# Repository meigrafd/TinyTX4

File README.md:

TinyTX4
=======

RFM12B based TinyTX Transmitter

Projekt Page: http://www.forum-raspberrypi.de/Thread-messen-steuern-regeln-batteriebetriebene-funk-sensoren

## Compiled Sketch size

#### with RFM12B lib:

Send_DHT22.ino --> 5.254 Bytes.  
Send_DHT22.ino & encrypt --> 6.896 Bytes.  
Send_DHT22_Watchdog.ino --> 5.512 Bytes.  
Send_DHT22_Watchdog.ino & encrypt --> 7.154 Bytes.  

Send_DS18B20.ino --> 7.342 Bytes.  
Send_DS18B20.ino & encrypt --> ... 768 bytes to big.  
Send_DS18B20_Watchdog.ino --> 7.590 Bytes.  
Send_DS18B20_Watchdog.ino & encrypt --> ... 1012 bytes to big.  

Send_ReedSwitch_Watchdog.ino --> 4.312 Bytes.  
Send_ReedSwitch_Watchdog.ino & encrypt --> 5.954 Bytes.  

#### with JeeLib:

Send_DHT22_Watchdog_JeeLib.ino --> 5.082 Bytes.  
Send_DHT22_Watchdog_JeeLib.ino & encrypt --> 6.746 Bytes.  

Send_DS18B20_Watchdog_JeeLib.ino --> 7.160 Bytes.  
Send_DS18B20_Watchdog_JeeLib.ino & encrypt --> ... 578 bytes to big.  

Send_ReedSwitch_Watchdog_JeeLib.ino --> 3.870 Bytes.  
Send_ReedSwitch_Watchdog_JeeLib.ino & encrypt --> 5.534 Bytes.  

Send_BMP085_Watchdog_JeeLib.ino --> 6.266 Bytes.  
Send_BMP085_Watchdog_JeeLib.ino & encrypt --> 7.894 Bytes.

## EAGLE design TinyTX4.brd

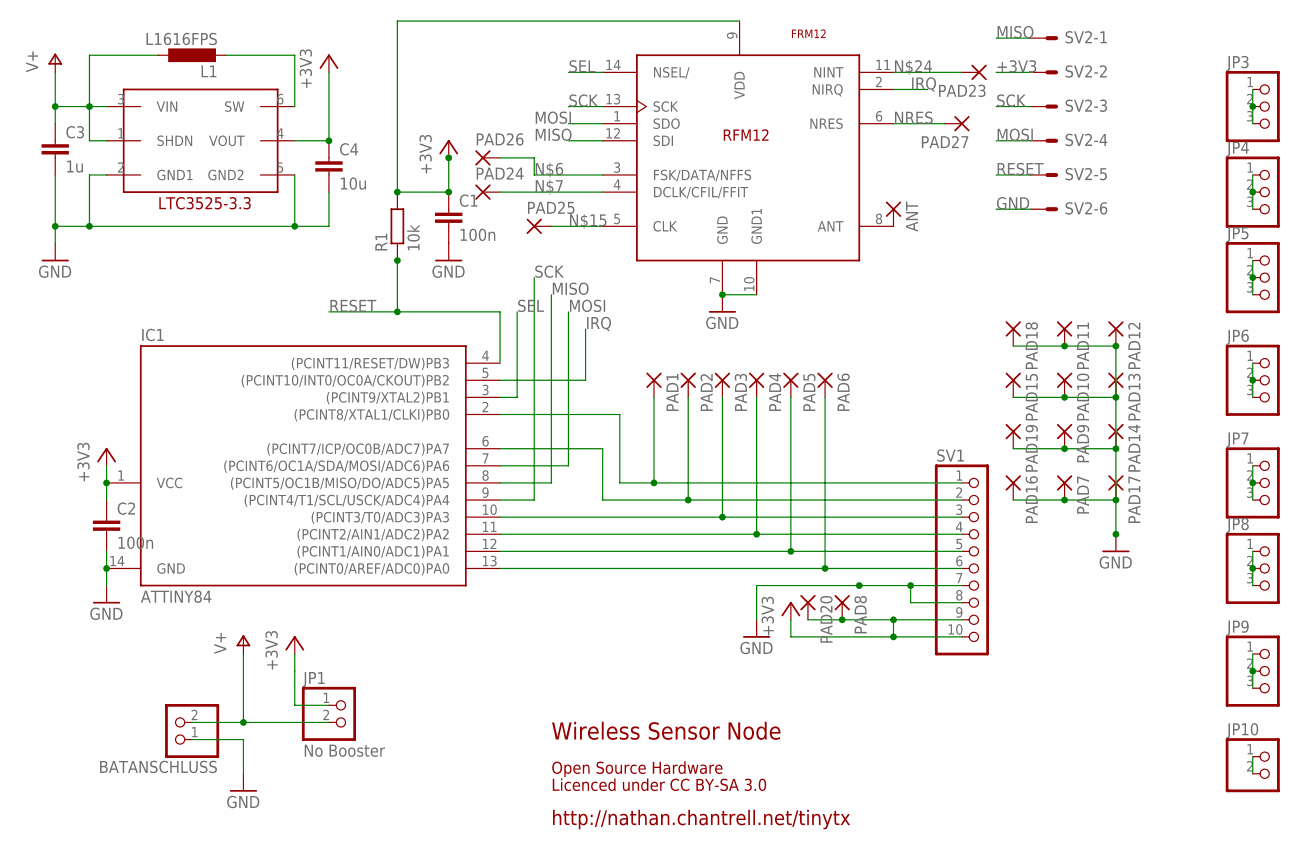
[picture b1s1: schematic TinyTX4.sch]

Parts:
ANT: 1,6/0,8
BATANSCHLUSS: PINHD-1X2; 1X02
C1, C2: 100n; C0805
C3: 1u; C0805
C4: 10u; C0805
IC1: ATTINY84; SOIC14
IC2: IC2; SC70-6
JP1: No Booster; 1X02
JP3, JP4, JP5, JP6, JP7, JP8, JP9: PINHD-1X3; 1X03
JP10: PINHD-1X2; 1X02
L1: L1616FPS; L1616
PAD1, PAD2, PAD3, PAD4, PAD5, PAD6, PAD7, PAD8, PAD9, PAD10, PAD11, PAD12, PAD13, PAD14, PAD15, PAD16, PAD17, PAD18, PAD19, PAD20, PAD23, PAD24, PAD25, PAD26, PAD27: 1,6/0,9
R1: 10k; R0805
SV1: PINHD-1X10; 1X10
SV2: ML6E; ML6
U$3: FRM12; RFM12

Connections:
+3V3: C1.1, C2.1, C4.1, IC1.1 (VCC), IC2.4 (VOUT), JP1.1, PAD8.1, PAD20.1, R1.2, SV1.9, SV1.10, SV2.2, U$3.9 (VDD)
ANT: ANT.1, U$3.8 (ANT)
GND: BATANSCHLUSS.1, C1.2, C2.2, C3.2, C4.2, IC1.14 (GND), IC2.2 (GND1), IC2.5 (GND2), PAD7.1, PAD9.1, PAD10.1, PAD11.1, PAD12.1, PAD13.1, PAD14.1, PAD15.1, PAD16.1, PAD17.1, PAD18.1, PAD19.1, SV1.7, SV1.8, SV2.6, U$3.7 (GND), U$3.10 (GND1)
IRQ: IC1.5 ((PCINT10/INT0/OC0A/CKOUT)PB2), U$3.2 (NIRQ)
MISO: IC1.8 ((PCINT5/OC1B/MISO/DO/ADC5)PA5), SV2.1, U$3.12 (SDI)
MOSI: IC1.7 ((PCINT6/OC1A/SDA/MOSI/ADC6)PA6), SV2.4, U$3.1 (SDO)
unnamed: PAD26.1, U$3.3 (FSK/DATA/NFFS)
unnamed: PAD24.1, U$3.4 (DCLK/CFIL/FFIT)
unnamed: IC1.6 ((PCINT7/ICP/OC0B/ADC7)PA7), PAD2.1, SV1.2
unnamed: IC1.13 ((PCINT0/AREF/ADC0)PA0), PAD6.1, SV1.6
unnamed: IC1.12 ((PCINT1/AIN0/ADC1)PA1), PAD5.1, SV1.5
unnamed: IC1.2 ((PCINT8/XTAL1/CLKI)PB0), PAD1.1, SV1.1
unnamed: IC2.6 (SW), L1.P$2 (2)
unnamed: IC1.11 ((PCINT2/AIN1/ADC2)PA2), PAD4.1, SV1.4
unnamed: IC1.10 ((PCINT3/T0/ADC3)PA3), PAD3.1, SV1.3
unnamed: PAD25.1, U$3.5 (CLK)
unnamed: JP3.1, JP3.2, JP3.3
unnamed: JP4.1, JP4.2, JP4.3
unnamed: JP5.1, JP5.2, JP5.3
unnamed: JP10.1, JP10.2
unnamed: JP6.1, JP6.2, JP6.3
unnamed: JP9.1, JP9.2, JP9.3
unnamed: JP7.1, JP7.2, JP7.3
unnamed: JP8.1, JP8.2, JP8.3
unnamed: PAD23.1, U$3.11 (NINT)
NRES: PAD27.1, U$3.6 (NRES)
RESET: IC1.4 ((PCINT11/RESET/DW)PB3), R1.1, SV2.5
SCK: IC1.9 ((PCINT4/T1/SCL/USCK/ADC4)PA4), SV2.3, U$3.13 (SCK)
SEL: IC1.3 ((PCINT9/XTAL2)PB1), U$3.14 (NSEL/)
V+: BATANSCHLUSS.2, C3.1, IC2.1 (SHDN), IC2.3 (VIN), JP1.2, L1.P$1 (1)

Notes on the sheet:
http://nathan.chantrell.net/tinytx
Wireless Sensor Node
Licenced under CC BY-SA 3.0
Open Source Hardware

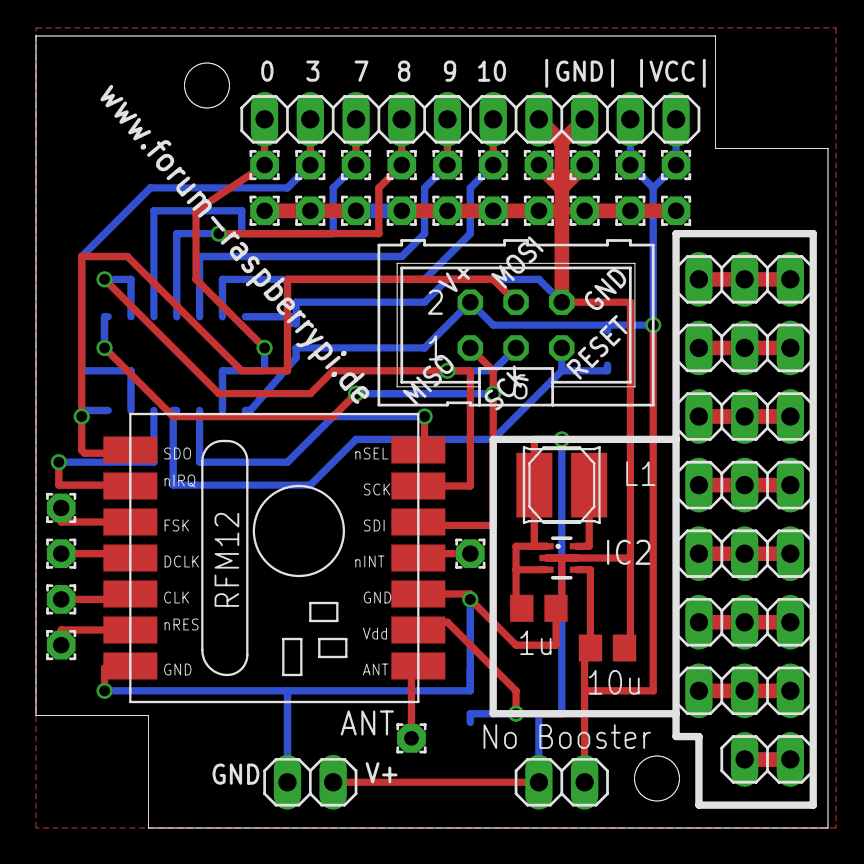
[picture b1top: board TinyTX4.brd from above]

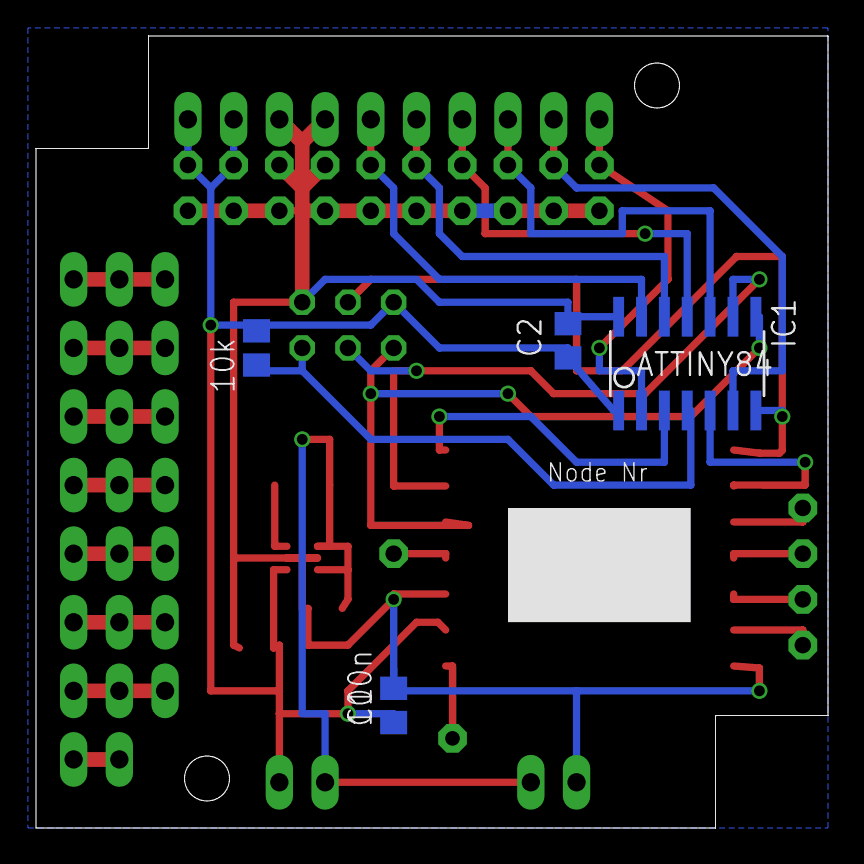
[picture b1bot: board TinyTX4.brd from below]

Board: 2 copper layers, 44.0 x 44.0 mm, 47 parts (4 on the bottom side), 30 nets.

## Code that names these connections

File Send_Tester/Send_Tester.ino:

// RFM12B Sender 
//
// Sketch to test functionality of Send.
// Sends static integer every 3 Sec. Requests ACK. Without power saving.
//
// modified by meigrafd @ 25.01.2015
//------------------------------------------------------------------------------
#include <RFM12B.h>

//------------------------------------------------------------------------------
// You will need to initialize the radio by telling it what ID it has and what network it's on
// The NodeID takes values from 1-127, 0 is reserved for sending broadcast messages (send to all nodes)
// The Network ID takes values from 0-255
// By default the SPI-SS line used is D10 on Atmega328. You can change it by calling .SetCS(pin) where pin can be {8,9,10}
#define NODEID          1   // network ID used for this unit
#define NETWORKID     210   // the network ID we are on
#define GATEWAYID      22   // the node ID we're sending to
#define FREQ  RF12_433MHZ   // Frequency of RFM12B module

#define ACK_TIME     2000   // # of ms to wait for an ack
#define requestACK   true   // request ACK? (true/false)
#define SENDDELAY    3000   // wait this many ms between sending packets.

//------------------------------------------------------------------------------
// PIN-Konfiguration 
//------------------------------------------------------------------------------
// LED pin
#define LEDpin 8         // D8, PA2 (ATtiny pin 11) - set to 0 to disable LED
//------------------------------------------------------------------------------
/*
                     +-\/-+
               VCC  1|    |14  GND
          (D0) PB0  2|    |13  AREF (D10)
          (D1) PB1  3|    |12  PA1 (D9)
       (PB3) RESET  4|    |11  PA2 (D8)
INT0  PWM (D2) PB2  5|    |10  PA3 (D7)
      PWM (D3) PA7  6|    |9   PA4 (D6) SCK
SDA   PWM (D4) PA6  7|    |8   PA5 (D5) PWM
                     +----+
*/

//encryption is OPTIONAL
//to enable encryption you will need to:
// - provide a 16-byte encryption KEY (same on all nodes that talk encrypted)
// - to call .Encrypt(KEY) to start encrypting
// - to stop encrypting call .Encrypt(NULL)
//#define KEY   "a4gBM69UZ03lQyK4"

// Need an instance of the Radio Module
RFM12B radio;

// Temperatur-String zum Versand per 433 Mhz
char msg[26];

//##############################################################################

static void activityLed (byte state, byte time = 0) {
  if (LEDpin) {
    pinMode(LEDpin, OUTPUT);
    if (time == 0) {
      digitalWrite(LEDpin, state);
    } else {
      digitalWrite(LEDpin, state);
      delay(time);
      digitalWrite(LEDpin, !state);
    }
  }
}

// blink led
static void blink (byte pin, byte n = 3) {
  if (LEDpin) {
    pinMode(pin, OUTPUT);
    for (byte i = 0; i < 2 * n; ++i) {
      delay(100);
      digitalWrite(pin, !digitalRead(pin));
    }
  }
}

//--------------------------------------------------------------------------------------------------
// Read current supply voltage (in mV)
//--------------------------------------------------------------------------------------------------
long readVcc() {
  // Read 1.1V reference against AVcc
  // set the reference to Vcc and the measurement to the internal 1.1V reference
  #if defined(__AVR_ATmega32U4__) || defined(__AVR_ATmega1280__) || defined(__AVR_ATmega2560__)
      ADMUX = _BV(REFS0) | _BV(MUX4) | _BV(MUX3) | _BV(MUX2) | _BV(MUX1);
  #elif defined (__AVR_ATtiny24__) || defined(__AVR_ATtiny44__) || defined(__AVR_ATtiny84__)
      ADMUX = _BV(MUX5) | _BV(MUX0);
  #elif defined (__AVR_ATtiny25__) || defined(__AVR_ATtiny45__) || defined(__AVR_ATtiny85__)
      ADMUX = _BV(MUX3) | _BV(MUX2);
  #else
      ADMUX = _BV(REFS0) | _BV(MUX3) | _BV(MUX2) | _BV(MUX1);
  #endif
  delay(2); // Wait for Vref to settle
  ADCSRA |= _BV(ADSC); // Start conversion
  while (bit_is_set(ADCSRA,ADSC)); // measuring
  uint8_t low  = ADCL; // must read ADCL first - it then locks ADCH
  uint8_t high = ADCH; // unlocks both
  long result = (high<<8) | low;
  //result = 1125300L / result; // Back-Calculate Vcc (in mV); 1125300 = 1.1*1023*1000
  result = 1126400L / result; // Back-calculate Vcc in mV
  return result;
}


//--------------------------------------------------------------------------------------------------

// init Setup
void setup() {
  // configure RFM12B
  radio.Initialize(NODEID, FREQ, NETWORKID);
  #ifdef KEY
    radio.Encrypt((byte*)KEY); //comment this out to disable encryption
  #endif
  radio.Control(0xC040); // Adjust low battery voltage to 2.2V
  radio.Sleep();         // sleep right away to save power

  analogReference(INTERNAL);   // Set the aref to the internal 1.1V reference

  if (LEDpin) {
    activityLed(1,1000); // LED on
  }
}

void wakeUp(){}

// Loop
void loop() {
  int supplyV = readVcc(); // Get supply voltage
  int testint = 1337;
  // msg-Variable mit Daten zum Versand fuellen, die spaeter an das WebScript uebergeben werden
  strcpy(msg, "v=");
  itoa(supplyV, &msg[strlen(msg)], 10);
  strcat(msg, "&msg=");
  itoa(testint, &msg[strlen(msg)], 10);

  // Send data via RF
  radio.Wakeup();
  radio.Send(GATEWAYID, (uint8_t *)msg, strlen(msg), requestACK);
  //radio.Send(GATEWAYID, &msg, sizeof(msg), requestACK);
  radio.SendWait(2);    //wait for RF to finish sending (2=standby mode, 3=power down)
  radio.Sleep();

  if (LEDpin) {
    blink(LEDpin, 2); // blink LED
  }
  delay(SENDDELAY);
}

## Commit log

2014-03-07 Public Build
2014-05-27 Layoutkorrektur
    Gehäuse für LT3525 auf SC70 geändert
2014-05-27 Layoutkorrektur - retry
    Gehäuse für LT3525 auf SC70 geändert. (2. Versuch)
2014-05-27 Update TinyTX4.brd
    Fix for LTC3525 Package Size from TSOT23 to SC70
2014-05-27 Update TinyTX4.sch
    Fix for LTC3525 Package Size from TSOT23 to SC70
2015-01-23 Added Sketches
2015-01-25 Added Send_Tester, for testing TX with static int, sending every 3sec
2015-01-25 testing TX with static int, sending every 3sec
2015-01-29 hopefully fixed
2015-02-01 added smaller Sketches with JeeLib instead of RFM12B-lib
2015-02-04 Screenshot added
2016-01-13 Create Send_SHT21_Watchdog
2016-01-14 Update Send_SHT21_Watchdog.ino
    Included a do/while loop to escape communication errors while reading humidity, resulting in negative humidity values.
